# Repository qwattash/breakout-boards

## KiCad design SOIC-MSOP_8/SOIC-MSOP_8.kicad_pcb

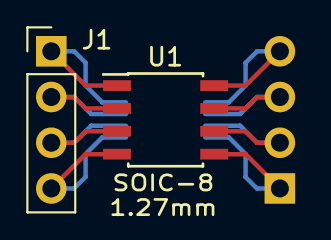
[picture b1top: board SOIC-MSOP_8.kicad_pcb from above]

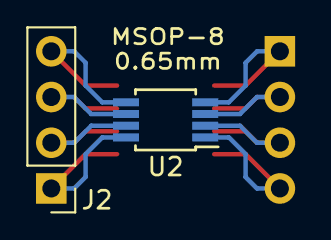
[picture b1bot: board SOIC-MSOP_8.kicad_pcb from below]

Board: 2 copper layers, 4 parts (2 on the bottom side), 8 nets.

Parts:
J1, J2: Conn_01x04; Pin_Header_Straight_1x04_Pitch2.54mm
U1: Generic_8pin; SOIC-8_3.9x4.9mm_Pitch1.27mm
U2: Generic_8pin; MSOP-8_3x3mm_Pitch0.65mm

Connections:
unnamed: J1.1, U1.1, U2.4
unnamed: J1.2, U1.2, U2.3
unnamed: J1.3, U1.3, U2.2
unnamed: J1.4, U1.4, U2.1
unnamed: J2.1, U1.5, U2.8
unnamed: J2.2, U1.6, U2.7
unnamed: J2.3, U1.7, U2.6
unnamed: J2.4, U1.8, U2.5

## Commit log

2020-02-12 Add initial breakout boards project.
2020-02-13 Add gitignore.
2020-02-13 Add breakout for TQFP-44 0.8mm pitch and TQFP-48 0.5mm pitch packages.
2020-02-13 Add SOIC-8 1.27mm pitch and MSOP-8 0.65mm pitch breakout.
